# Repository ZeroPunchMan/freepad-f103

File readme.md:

# 使用说明

## 校准步骤
```
1.松开全部按键和摇杆,长按配对键(USB插孔旁).
2.等LED出现呼吸灯效果,此时程序会等待摇杆和扳机稳定,并记录作为初始值.
3.一直等待至LED出现快速闪烁效果,此时表示初始值已记录完毕,开始记录边界值.
4.把左右扳机按到底部,同时把两个摇杆摇圈.
5.待LED变成呼吸灯效果后,再重复数次,短按A键并松开.
6.LED恢复常亮,校准完毕.
```

## 重置校准值
```
同上面校准步骤,但第4步改为如下操作:
4.按住Y键.
5.等LED恢复为常亮,校准值重置完毕.
```

## 升级固件步骤
```
1.拔掉手柄USB线.
2.按住配对键(USB插孔旁).
3.插入USB线.
4.观察到LED较慢闪烁,表明手柄已进入BOOT状态.
5.打开DFU软件,选择对应串口并打开.
6.选择APP固件及其签名,点击开始升级.
7.提示升级成功则完毕.
```

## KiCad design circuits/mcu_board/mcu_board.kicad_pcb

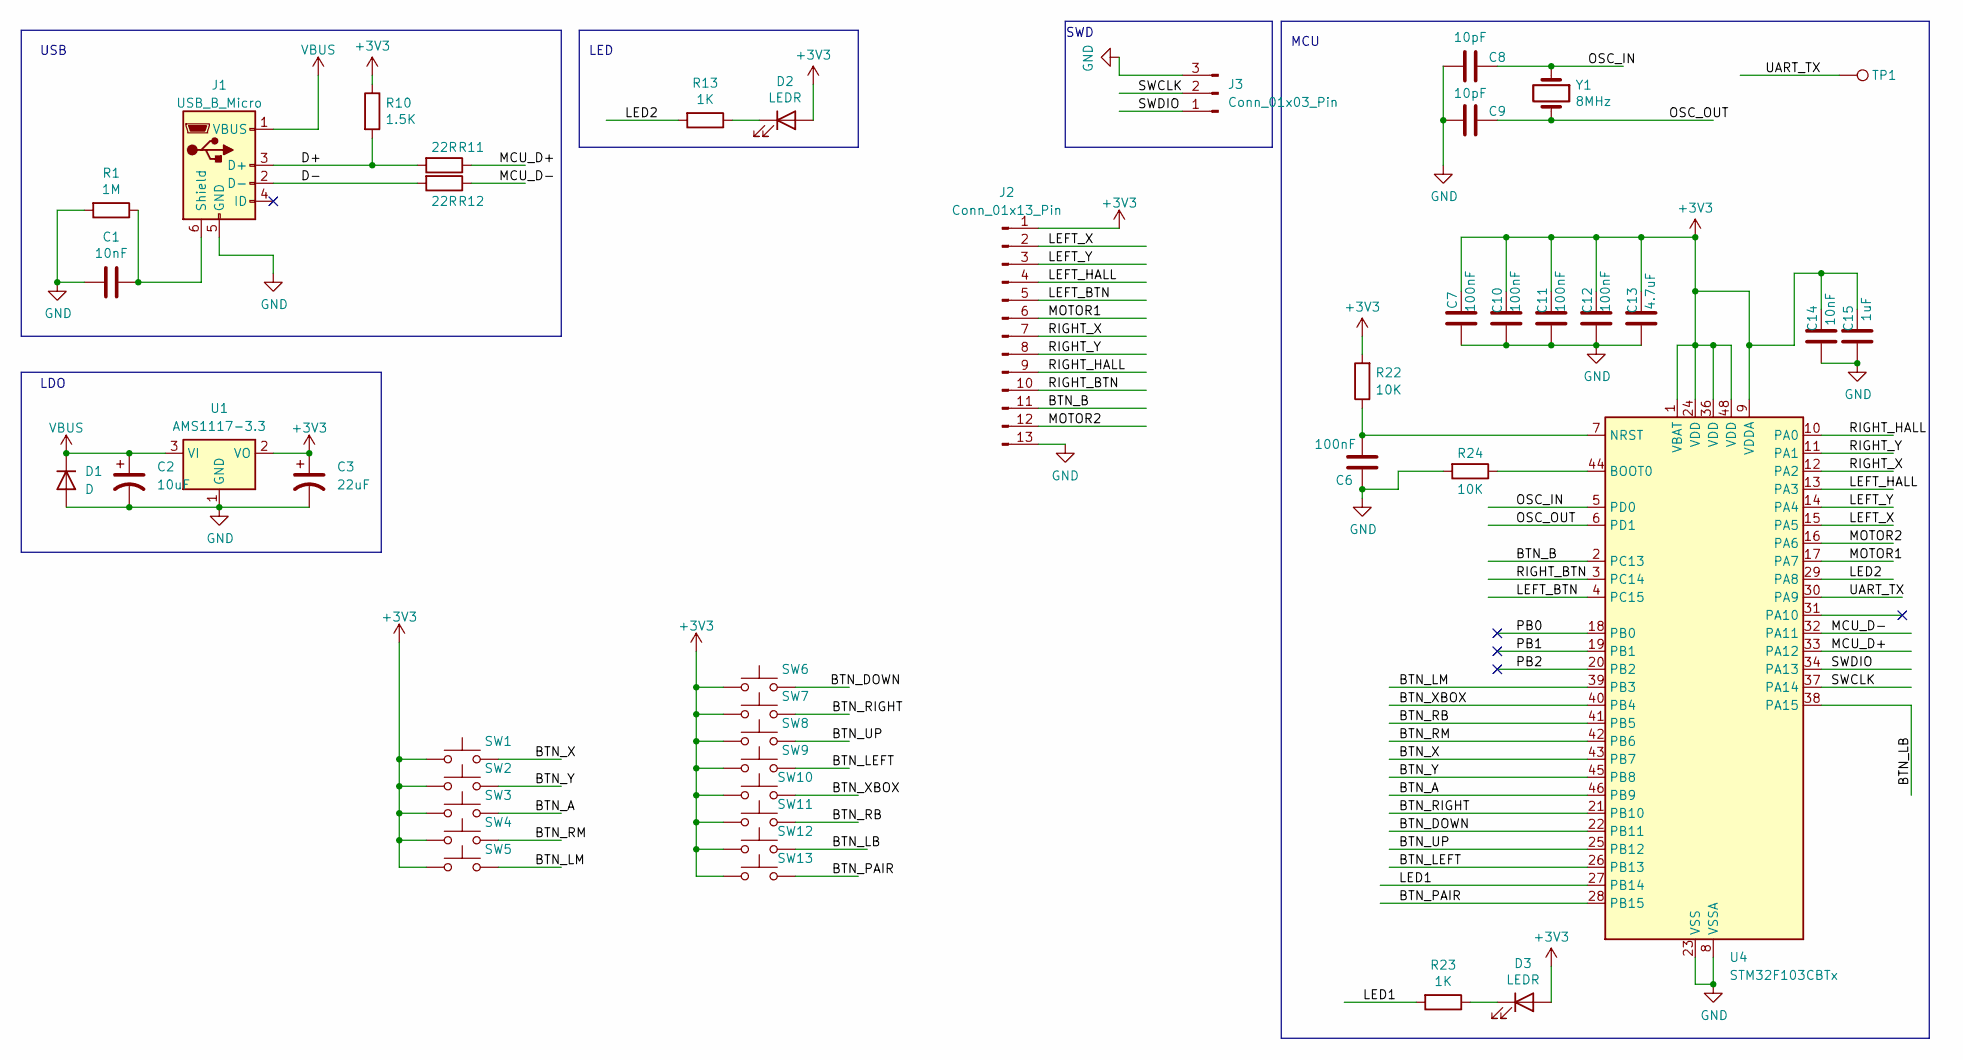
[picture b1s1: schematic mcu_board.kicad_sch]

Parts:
C1, C14: 10nF; C_0805_2012Metric_Pad1.18x1.45mm_HandSolder
C2: 10uF; C_1206_3216Metric_Pad1.33x1.80mm_HandSolder
C3: 22uF; C_1206_3216Metric_Pad1.33x1.80mm_HandSolder
C6, C7, C10, C11, C12: 100nF; C_0805_2012Metric_Pad1.18x1.45mm_HandSolder
C8, C9: 10pF; C_0805_2012Metric_Pad1.18x1.45mm_HandSolder
C13: 4.7uF; C_0805_2012Metric_Pad1.18x1.45mm_HandSolder
C15: 1uF; C_0805_2012Metric_Pad1.18x1.45mm_HandSolder
D1: D; D_2010_5025Metric_Pad1.52x2.65mm_HandSolder
D2, D3: LEDR; LED_0805_2012Metric_Pad1.15x1.40mm_HandSolder
J1: USB_B_Micro; USB_MICRO
J2: Conn_01x13_Pin; Molex_200528-0130_1x13-1MP_P1.00mm_Horizontal
J3: Conn_01x03_Pin; PinHeader_1x03_P2.54mm_Vertical
R1: 1M; R_0805_2012Metric_Pad1.20x1.40mm_HandSolder
R10: 1.5K; R_0805_2012Metric_Pad1.20x1.40mm_HandSolder
R11, R12: 22R; R_0805_2012Metric_Pad1.20x1.40mm_HandSolder
R13, R23: 1K; R_0805_2012Metric_Pad1.20x1.40mm_HandSolder
R22, R24: 10K; R_0805_2012Metric_Pad1.20x1.40mm_HandSolder
SW1, SW2, SW3, SW4, SW5: SW_Push; touch
SW6, SW7, SW8, SW9: SW_Push; touch-dpad
SW10: SW_Push; touch-xbox
SW11, SW12: SW_Push; click_lbrb
SW13: SW_Push; click_pair
TP1: TestPoint; TestPoint_Pad_1.0x1.0mm
U1: AMS1117-3.3; SOT-223-3_TabPin2
U4: STM32F103CBTx; LQFP-48_7x7mm_P0.5mm
Y1: 8MHz; Crystal_SMD_5032-2Pin_5.0x3.2mm_HandSoldering

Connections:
+3V3: C3.1, C7.1, C10.1, C11.1, C12.1, C13.1, C14.1, C15.1, D2.2 (A), D3.2 (A), J2.1, R10.1, R22.2, SW1.1, SW2.1, SW3.1, SW4.1, SW5.1, SW6.1, SW7.1, SW8.1, SW9.1, SW10.1, SW11.1, SW12.1, SW13.1, U1.2 (VO), U4.1 (VBAT), U4.9 (VDDA), U4.24 (VDD), U4.36 (VDD), U4.48 (VDD)
/BTN_A: SW3.2, U4.46 (PB9)
/BTN_B: J2.11, U4.2 (PC13)
/BTN_DOWN: SW6.2, U4.22 (PB11)
/BTN_LB: SW12.2, U4.38 (PA15)
/BTN_LEFT: SW9.2, U4.26 (PB13)
/BTN_LM: SW5.2, U4.39 (PB3)
/BTN_PAIR: SW13.2, U4.28 (PB15)
/BTN_RB: SW11.2, U4.41 (PB5)
/BTN_RIGHT: SW7.2, U4.21 (PB10)
/BTN_RM: SW4.2, U4.42 (PB6)
/BTN_UP: SW8.2, U4.25 (PB12)
/BTN_X: SW1.2, U4.43 (PB7)
/BTN_XBOX: SW10.2, U4.40 (PB4)
/BTN_Y: SW2.2, U4.45 (PB8)
/D+: J1.3 (D+), R10.2, R11.2
/D-: J1.2 (D-), R12.2
/LED1: R23.2, U4.27 (PB14)
/LED2: R13.2, U4.29 (PA8)
/LEFT_BTN: J2.5, U4.4 (PC15)
/LEFT_HALL: J2.4, U4.13 (PA3)
/LEFT_X: J2.2, U4.15 (PA5)
/LEFT_Y: J2.3, U4.14 (PA4)
/MCU_D+: R11.1, U4.33 (PA12)
/MCU_D-: R12.1, U4.32 (PA11)
/MOTOR1: J2.6, U4.17 (PA7)
/MOTOR2: J2.12, U4.16 (PA6)
/OSC_IN: C8.1, U4.5 (PD0), Y1.1
/OSC_OUT: C9.1, U4.6 (PD1), Y1.2
/PB0: U4.18 (PB0)
/PB1: U4.19 (PB1)
/PB2: U4.20 (PB2)
/RIGHT_BTN: J2.10, U4.3 (PC14)
/RIGHT_HALL: J2.9, U4.10 (PA0)
/RIGHT_X: J2.7, U4.12 (PA2)
/RIGHT_Y: J2.8, U4.11 (PA1)
/SWCLK: J3.2, U4.37 (PA14)
/SWDIO: J3.1, U4.34 (PA13)
/UART_TX: TP1.1, U4.30 (PA9)
GND: C1.2, C2.2, C3.2, C6.2, C7.2, C8.2, C9.2, C10.2, C11.2, C12.2, C13.2, C14.2, C15.2, D1.2 (A), J1.5 (GND), J2.13, J3.3, R1.2, R24.2, U1.1 (GND), U4.8 (VSSA), U4.23 (VSS), U4.35 (VSS), U4.47 (VSS)
unnamed: D2.1 (K), R13.1
unnamed: D3.1 (K), R23.1
unnamed: C1.1, J1.6 (Shield), R1.1
unnamed: R24.1, U4.44 (BOOT0)
unnamed: C6.1, R22.1, U4.7 (NRST)
VBUS: C2.1, D1.1 (K), J1.1 (VBUS), U1.3 (VI)

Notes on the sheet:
LDO
USB
SWD
MCU
LED

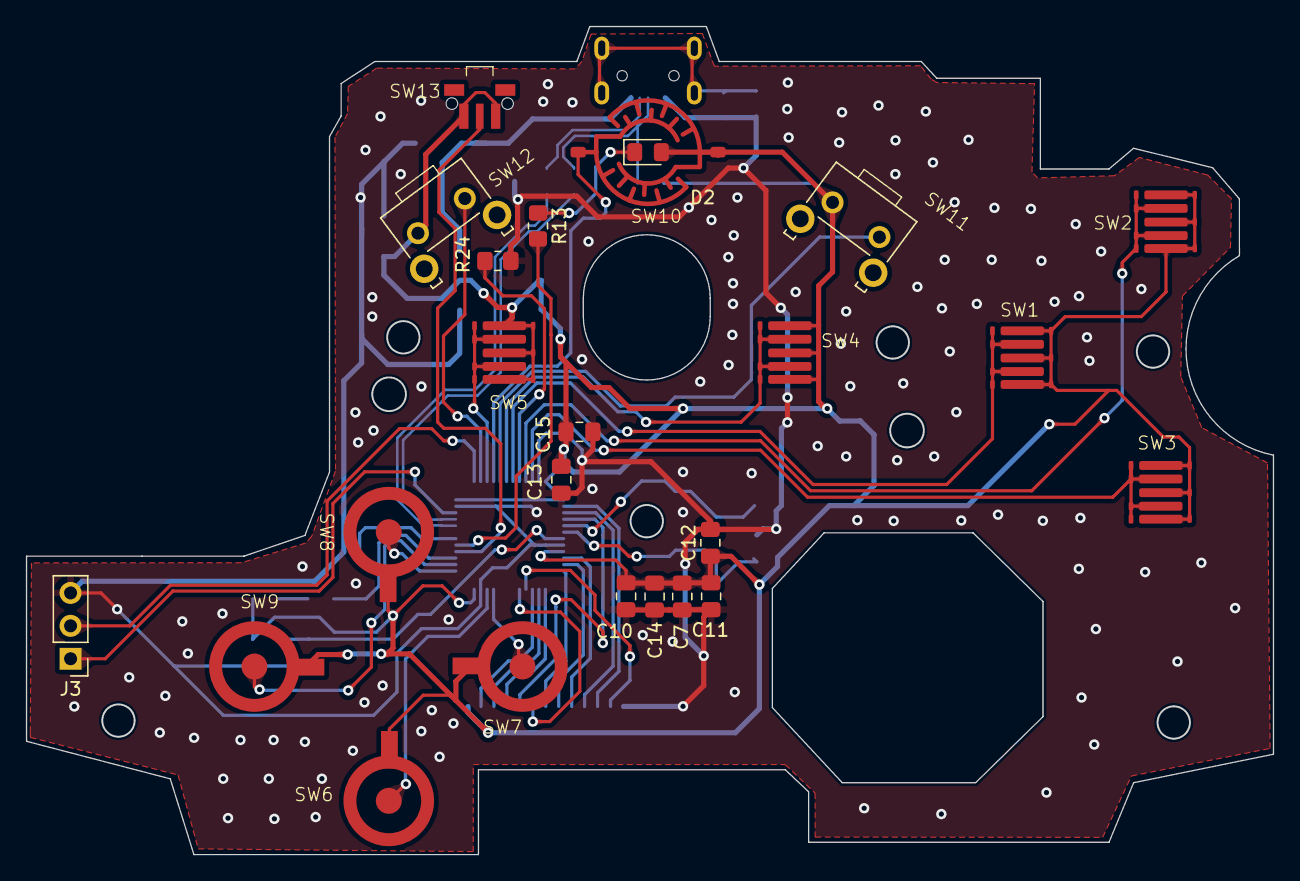
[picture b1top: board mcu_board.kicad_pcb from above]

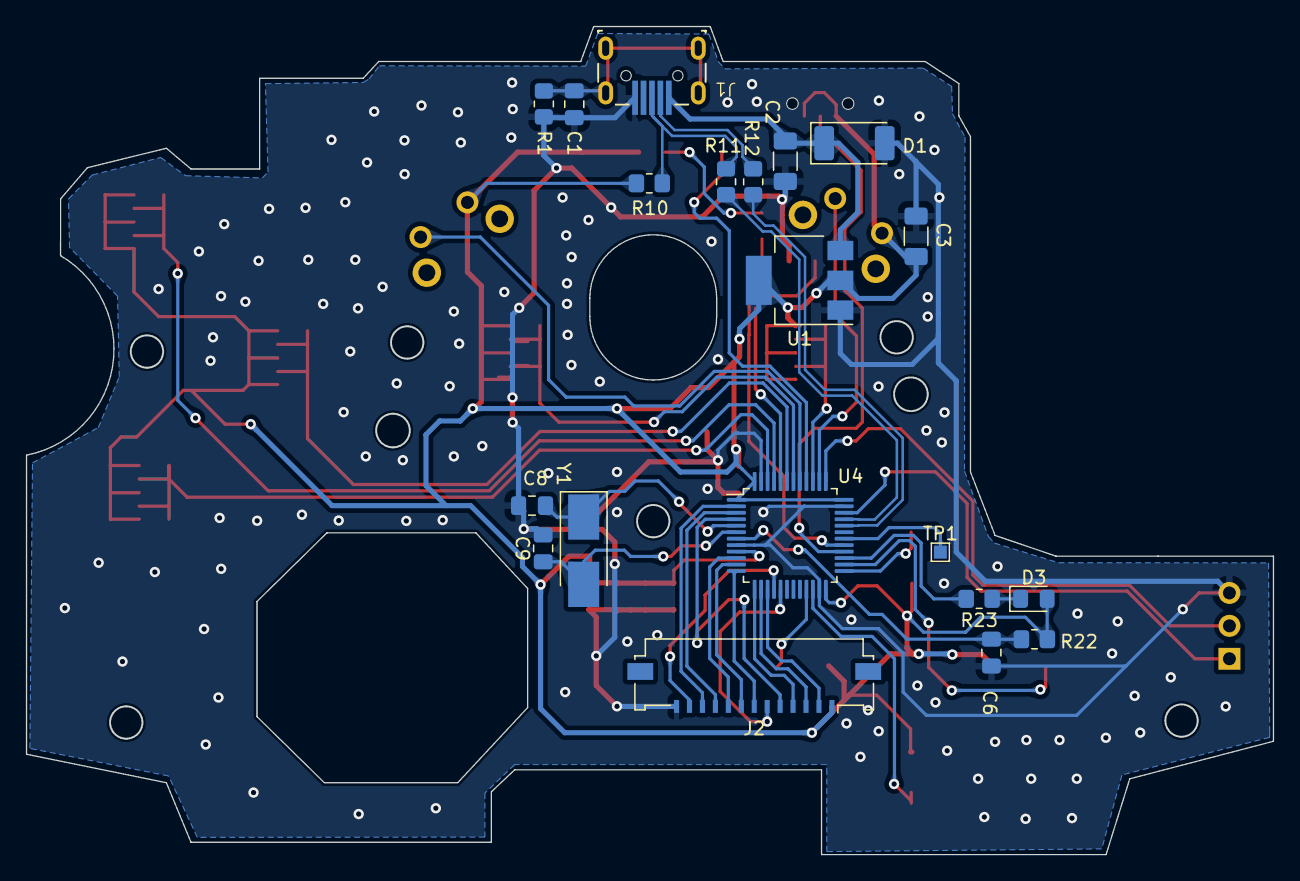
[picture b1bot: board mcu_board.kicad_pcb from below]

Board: 2 copper layers, 96.3 x 63.9 mm, 44 parts (20 on the bottom side), 43 nets.

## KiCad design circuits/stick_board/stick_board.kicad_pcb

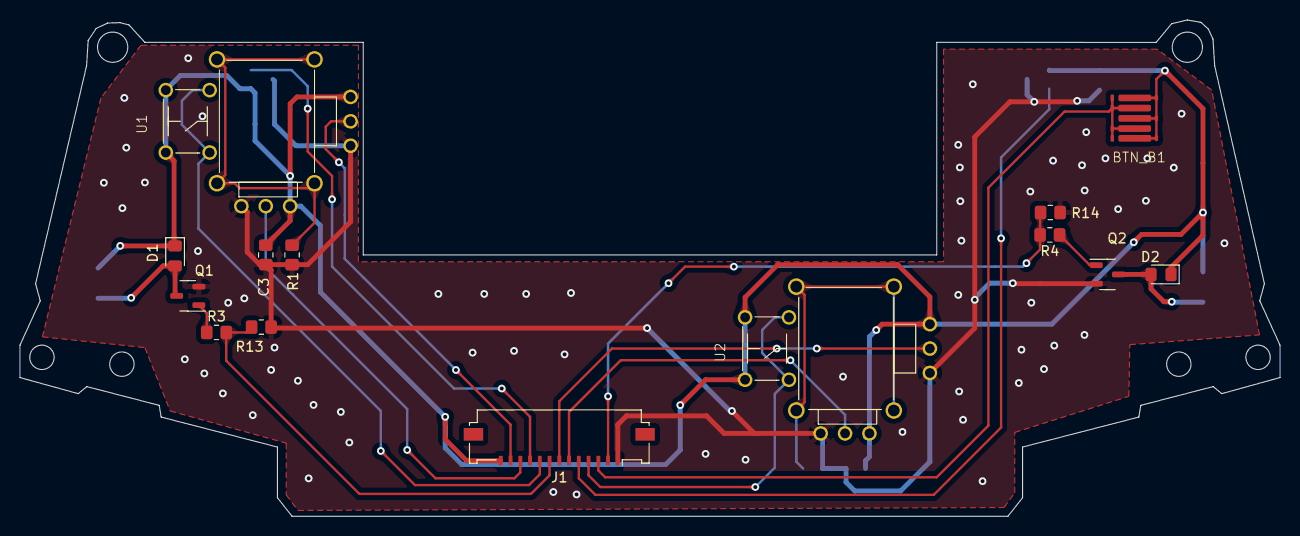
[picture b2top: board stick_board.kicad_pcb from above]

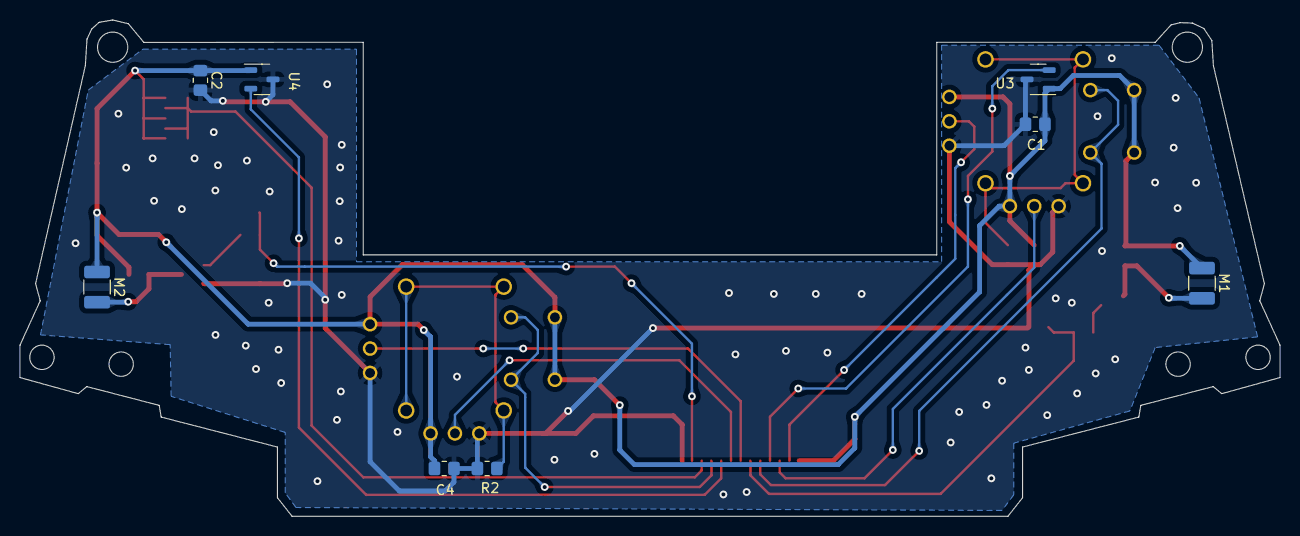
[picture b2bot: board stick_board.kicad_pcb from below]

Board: 2 copper layers, 129.2 x 50.9 mm, 22 parts (8 on the bottom side), 19 nets.

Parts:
BTN_B1: SW_PUSH; touch
C1, C2, C3, C4: 100nF; R_0805_2012Metric_Pad1.20x1.40mm_HandSolder
D1, D2: D; D_0805_2012Metric_Pad1.15x1.40mm_HandSolder
J1: Conn_01x13_Pin; Molex_200528-0130_1x13-1MP_P1.00mm_Horizontal
M1, M2: Motor_DC; R_1210_3225Metric_Pad1.30x2.65mm_HandSolder
Q1, Q2: AO3400A; SOT-23-3
R1, R2: 1M; R_0805_2012Metric_Pad1.20x1.40mm_HandSolder
R3, R4: 1K; R_0805_2012Metric_Pad1.20x1.40mm_HandSolder
R13, R14: 10K; R_0805_2012Metric_Pad1.20x1.40mm_HandSolder
U1, U2: GULI
U3, U4: DRV5055A1xDBZxQ1; SOT-23-3

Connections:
+3V3: BTN_B1.1, C1.1, C2.1, C3.1, C4.1, D1.1 (K), D2.1 (K), J1.13, M1.1 (+), M2.1 (+), U1.2 (VDD), U1.5 (SW_2), U2.2 (VDD), U2.5 (SW_2), U3.1 (VCC), U4.1 (VCC)
/BTN_B: BTN_B1.2, J1.3
/LEFT_BTN: J1.9, U1.4 (SW_1)
/LEFT_HALL: J1.10, U3.2 (OUT)
/LEFT_X: J1.12, U1.7 (X)
/LEFT_Y: J1.11, U1.6 (Y)
/MOTOR1: J1.8, R3.2, R13.2
/MOTOR2: J1.2, R4.2, R14.2
/RIGHT_BTN: J1.4, U2.4 (SW_1)
/RIGHT_HALL: J1.5, U4.2 (OUT)
/RIGHT_X: J1.7, U2.7 (X)
/RIGHT_Y: J1.6, U2.6 (Y)
GND: C1.2, C2.2, C3.2, C4.2, J1.1, Q1.2 (S), Q2.2 (S), R1.1, R2.1, R13.1, R14.1, U1.1 (GND), U2.1 (GND), U3.3 (GND), U4.3 (GND)
unnamed: D1.2 (A), M1.2 (-), Q1.3 (D)
unnamed: D2.2 (A), M2.2 (-), Q2.3 (D)
unnamed: Q1.1 (G), R3.1
unnamed: Q2.1 (G), R4.1
unnamed: R1.2, U1.3 (Shield)
unnamed: R2.2, U2.3 (Shield)

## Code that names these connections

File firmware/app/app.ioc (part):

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Mcu.Name=STM32F103C(8-B)Tx
Mcu.Package=LQFP48
Mcu.UserName=STM32F103CBTx
PA0-WKUP.Signal=ADCx_IN0
PA1.Signal=ADCx_IN1
PA10.Mode=Asynchronous
PA10.Signal=USART1_RX
PA11.Mode=Device
PA11.Signal=USB_DM
PA12.Mode=Device
PA12.Signal=USB_DP
PA15.GPIOParameters=GPIO_PuPd
PA15.GPIO_PuPd=GPIO_PULLDOWN
PA15.Signal=GPIO_Input
PA2.Signal=ADCx_IN2
PA3.Signal=ADCx_IN3
PA4.Signal=ADCx_IN4
PA5.Signal=ADCx_IN5
PA6.Signal=S_TIM3_CH1
PA7.Signal=S_TIM3_CH2
PA8.Signal=S_TIM1_CH1
PA9.Mode=Asynchronous
PA9.Signal=USART1_TX
PB10.GPIOParameters=GPIO_PuPd
PB10.GPIO_PuPd=GPIO_PULLDOWN
PB10.Signal=GPIO_Input
PB11.GPIOParameters=GPIO_PuPd
PB11.GPIO_PuPd=GPIO_PULLDOWN
PB11.Signal=GPIO_Input
PB12.GPIOParameters=GPIO_PuPd
PB12.GPIO_PuPd=GPIO_PULLDOWN
PB12.Signal=GPIO_Input
PB13.GPIOParameters=GPIO_PuPd
PB13.GPIO_PuPd=GPIO_PULLDOWN
PB13.Signal=GPIO_Input
PB14.GPIOParameters=GPIO_PuPd
PB14.GPIO_PuPd=GPIO_PULLUP
PB14.Signal=GPIO_Output
PB15.GPIOParameters=GPIO_PuPd
PB15.GPIO_PuPd=GPIO_PULLDOWN
PB15.Signal=GPIO_Input
PB3.GPIOParameters=GPIO_PuPd
PB3.GPIO_PuPd=GPIO_PULLDOWN
PB3.Signal=GPIO_Input
PB4.GPIOParameters=GPIO_PuPd
PB4.GPIO_PuPd=GPIO_PULLDOWN
PB4.Signal=GPIO_Input
PB5.GPIOParameters=GPIO_PuPd
PB5.GPIO_PuPd=GPIO_PULLDOWN
PB5.Signal=GPIO_Input
PB6.GPIOParameters=GPIO_PuPd
PB6.GPIO_PuPd=GPIO_PULLDOWN
PB6.Signal=GPIO_Input
PB7.GPIOParameters=GPIO_PuPd
PB7.GPIO_PuPd=GPIO_PULLDOWN
PB7.Signal=GPIO_Input
PB8.GPIOParameters=GPIO_PuPd
PB8.GPIO_PuPd=GPIO_PULLDOWN
PB8.Signal=GPIO_Input
PB9.GPIOParameters=GPIO_PuPd
PB9.GPIO_PuPd=GPIO_PULLDOWN
PB9.Signal=GPIO_Input
PC13-TAMPER-RTC.GPIOParameters=GPIO_PuPd
PC13-TAMPER-RTC.GPIO_PuPd=GPIO_PULLDOWN
PC13-TAMPER-RTC.Signal=GPIO_Input
PC14-OSC32_IN.GPIOParameters=GPIO_PuPd
PC14-OSC32_IN.GPIO_PuPd=GPIO_PULLDOWN
PC14-OSC32_IN.Signal=GPIO_Input
PC15-OSC32_OUT.GPIOParameters=GPIO_PuPd
PC15-OSC32_OUT.GPIO_PuPd=GPIO_PULLDOWN
PC15-OSC32_OUT.Signal=GPIO_Input
PD0-OSC_IN.Mode=HSE-External-Oscillator
PD0-OSC_IN.Signal=RCC_OSC_IN
PD1-OSC_OUT.Mode=HSE-External-Oscillator
PD1-OSC_OUT.Signal=RCC_OSC_OUT
RCC.SYSCLKFreq_VALUE=72000000
RCC.SYSCLKSource=RCC_SYSCLKSOURCE_PLLCLK
board=custom

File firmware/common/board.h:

#pragma once

#include "main.h"

#define GPIO_APB (LL_APB2_GRP1_PERIPH_GPIOB)

#define STA_LED_PROT (GPIOB)
#define STA_LED_PIN (LL_GPIO_PIN_14)

//**************按键****************
#define BTN_B_PORT (GPIOC)
#define BTN_B_PIN (LL_GPIO_PIN_13)

#define BTN_RSTICK_PORT (GPIOC)
#define BTN_RSTICK_PIN (LL_GPIO_PIN_14)

#define BTN_LSTICK_PORT (GPIOC)
#define BTN_LSTICK_PIN (LL_GPIO_PIN_15)

#define BTN_LMENU_PORT (GPIOB)
#define BTN_LMENU_PIN (LL_GPIO_PIN_3)

#define BTN_XBOX_PORT (GPIOB)
#define BTN_XBOX_PIN (LL_GPIO_PIN_4)

#define BTN_RB_PORT (GPIOB)
#define BTN_RB_PIN (LL_GPIO_PIN_5)

#define BTN_RMENU_PORT (GPIOB)
#define BTN_RMENU_PIN (LL_GPIO_PIN_6)

#define BTN_X_PORT (GPIOB)
#define BTN_X_PIN (LL_GPIO_PIN_7)

#define BTN_Y_PORT (GPIOB)
#define BTN_Y_PIN (LL_GPIO_PIN_8)

#define BTN_A_PORT (GPIOB)
#define BTN_A_PIN (LL_GPIO_PIN_9)

#define BTN_RIGHT_PORT (GPIOB)
#define BTN_RIGHT_PIN (LL_GPIO_PIN_10)

#define BTN_DOWN_PORT (GPIOB)
#define BTN_DOWN_PIN (LL_GPIO_PIN_11)

#define BTN_UP_PORT (GPIOB)
#define BTN_UP_PIN (LL_GPIO_PIN_12)

#define BTN_LEFT_PORT (GPIOB)
#define BTN_LEFT_PIN (LL_GPIO_PIN_13)

#define BTN_PAIR_PORT (GPIOB)
#define BTN_PAIR_PIN (LL_GPIO_PIN_15)

#define BTN_LB_PORT (GPIOA)
#define BTN_LB_PIN (LL_GPIO_PIN_15)

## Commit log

2023-09-01 boot cdc
2023-09-01 clib added
2023-09-01 串口打印日志,未测试
2023-09-01 mmlib added
2023-09-01 clib 配置; systime计时
2023-09-01 log and usb ok
2023-09-03 comm收发,未测试
2023-09-03 flash 报错
2023-09-03 comm初步测试ok
2023-09-03 dfu签名,不用备份区
2023-09-03 boot 初步完成,未测试
2023-09-03 app added
2023-09-03 app打印ok
2023-09-03 修改app启动地址
2023-09-03 增加app跳转判断
2023-09-04 升级协议初步ok
2023-09-04 boot 加上led
2023-09-04 hid 枚举成功
2023-09-04 单个按键测试ok
2023-09-05 boot vid pid string
2023-09-06 调整flash布局,增加一页存储pad参数
2023-09-06 增加pad_func
2023-09-06 out report接收
2023-09-07 hc165逻辑未实现
2023-09-07 加入adc和pwm
2023-09-08 HC165写完,未测试
2023-09-08 usb配置
2023-09-08 adc-dma中断触发了2次
2023-09-08 adc改用ll库,未完成
2023-09-08 adc dma中断
2023-09-08 关USB低功耗
2023-09-08 关usb low power
2023-09-09 按键扫描ok
2023-09-10 adc 摇杆ok
2023-09-10 add circuits
2023-09-10 add mcu board
2023-09-10 usb footprint
2023-09-11 增加键值映射,未测试
2023-09-11 pwm和led初步测试ok
2023-09-11 button和cali未完成
2023-09-11 校准流程未完成
2023-09-12 完成校准流程,未测试
2023-10-07 right trigger
2023-10-07 use cubemx hid
2023-10-07 360枚举成功
2023-10-07 修改序列化
2023-10-07 初步测试ok
2023-10-07 需改按键映射测试 需测试校准流程
2023-10-08 HC165处理
2023-10-08 重命名, 增加震动处理
2023-10-08 增加马达限流电阻
2023-10-09 报告序列化测试ok
2023-10-09 测试板摇杆和按键映射测试ok
2023-10-09 校准流程和led测试ok，
2023-10-11 layout 23.10.11
2023-10-14 layout 摇杆板轮廓
2023-10-14 layout 摇杆板布局ok
2023-10-14 layout 摇杆板完成
2023-10-15 layout 摇杆板优化马达驱动,增加覆铜过孔 MCU板改动
2023-10-15 layout 增加摇杆板孔径
2023-10-15 mcu板 螺丝孔位置需验证
2023-10-15 layout MCU板大致形状
2023-10-17 layout 增加lb/rb和pair按键封装 空间不够需精简电路
2023-10-17 更新mcu板原理图,改晶振封装
2023-10-18 mcu板极端精简电路
2023-10-19 laytou MCU板基本完成走线
2023-10-19 更新按键封装，不用开窗
2023-10-19 移除两个马达PWM完成 移除HC165未完成
2023-10-19 按键逻辑修改完成,未测试
2023-10-19 GPIO改下拉
2023-10-19 状态led控制脚上拉
2023-10-19 stick板添加泪滴
2023-10-19 layout mcu板边界优化
2023-10-20 摇杆板添加大量GND过孔
2023-10-21 螺丝孔位置确定，xbox键位置确定
2023-10-21 dpad位置对准
2023-10-21 剩下lb rb位置未确定
2023-10-21 布局基本确定
2023-10-21 layout未完成
2023-10-22 MCU板layout完成
2023-10-22 减少stick板孔径
2023-10-22 缩小MCU板孔径
2023-10-22 优化stick板边缘
2023-10-23 mcu板按键封装修改,添加泪滴和覆铜间距
2023-10-23 调整mcu板覆铜间隙,消除警告
2023-10-23 更新stick板按键封装
2023-10-23 修改单片机型号
2023-10-23 修改按键映射
2023-10-25 按键检测有问题
2023-10-25 通过log测试按键ok
2023-10-25 更新摇杆板触摸键封装
2023-10-25 手柄板更新按键封装
2023-10-25 mcu板更新封装
2023-10-29 马达驱动增加栅极电阻
2023-10-29 更新按键封装
2023-10-29 差手柄机械按键位置
2023-10-29 调整封装,待打样测试
2023-10-29 微调了LB RB位置
2023-10-29 微调LB RB
2023-10-29 微调MCU版USB信号线，增加过孔
2023-11-01 修改ADC映射
2023-11-02 app启动地址修改
2023-11-03 LED PWM反向
2023-11-03 震动测试ok
2023-11-03 增加校准复位流程,未测试
2023-11-04 boot修改灯
2023-11-04 提高马达输出占空比
2023-11-04 mcu板排线座子位置优化
2023-11-04 stick板去除马达限流电阻
2023-11-04 xbox按键需要加粗
2023-11-04 xbox按键线条加粗
2023-11-04 优化mcu板尺寸
2023-11-05 优化布局
2023-11-05 ldo位置优化
2023-11-12 优化布局,准备用沉金工艺
2023-11-12 过孔位置优化
2023-11-15 增加APP版本信息
2023-11-15 boot中增加APP版本获取,未测试
2023-11-16 微调螺丝孔
2023-11-16 增加泪滴
2023-11-19 not done
2023-11-19 优化元件位置,防止外壳挤压
2023-11-20 晶振下移一点
2023-11-28 增加readme说明操作步骤
2023-11-28 增加readme升级说明,注释todo未做的远程唤醒
2023-12-01 代码review问题修复
2023-12-08 微调电阻位置
2023-12-13 更新log模块,未测试
2023-12-13 boot更新log模块
2023-12-13 更新log模块
2023-12-13 log增加换行
2023-12-14 精简log app
2023-12-14 精简log boot
2024-01-09 HID传输完成ep判断
2024-01-22 扳机插值改为立方根
2024-01-22 平方或立方插值
2024-01-24 boot版本修改
2024-01-24 摇杆改为平方根插值
2024-01-24 摇杆改回线性插值
2024-01-25 改电容位置,避免碰到遥感帽
2024-02-17 校准算法修改,未测试
2024-02-17 优化弧度计算
2024-02-17 多个点插值，初步测试ok
2024-02-17 校准完成时的LED提示,增加扳机判断
2024-02-18 优化边界值计算
2024-02-18 去掉acosf返回值范围限制
2024-02-20 精简校准代码,未测试
2024-02-20 摇杆改为60个角度并放大6%
2024-02-20 索引取余数,防止溢出
2024-02-21 更新readme
2024-03-01 摇杆和扳机增加死区
2024-03-01 调整扳机死区阈值
2024-03-01 v0.0.5
2024-03-01 update cmathex
2024-03-01 增加注释,优化摇杆换算减少浮点运算
2024-03-05 优化摇杆死区逻辑
2024-03-05 1.上报时增加USB空闲判断,减少无用计算 2.增加摇杆修正测试,用来验证修正值的角度
2024-03-07 移除测试代码
2024-09-27 删除clib旧配置
2024-09-27 修正log
